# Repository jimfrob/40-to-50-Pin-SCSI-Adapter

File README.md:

I had a spare PowerBook version of a BlueSCSI v2 and wanted to make use of it, so I designed a PCB to adapt the 40-pin connector of the PowerBook to the standard 50-pin connector. I then designed a mount for installing it in a computer. The BlueSCSI is intended to be soldered on top of the board with the 40-pin header between. The power connector may be extranneous since the BlueSCSI should be able to take termination power.

40-pin header: Digikey part number [62004021121](https://www.digikey.com/en/products/detail/würth-elektronik/62004021121/15672211?s=N4IgTCBcDaIGxgAyICyLARg5kBdAvkA)

50-pin header: Digikey part number [SBH11-PBPC-D25-ST-BK](https://www.digikey.com/en/products/detail/sullins-connector-solutions/SBH11-PBPC-D25-ST-BK/1990069?s=N4IgTCBcDaIMoCEASBGFBaACgzBhdAImAKzpwAq6CA0iALoC%2BQA)

Any 4-pin header should work for power for use with a floppy drive berg connector.

The board was designed with KiCad 8.

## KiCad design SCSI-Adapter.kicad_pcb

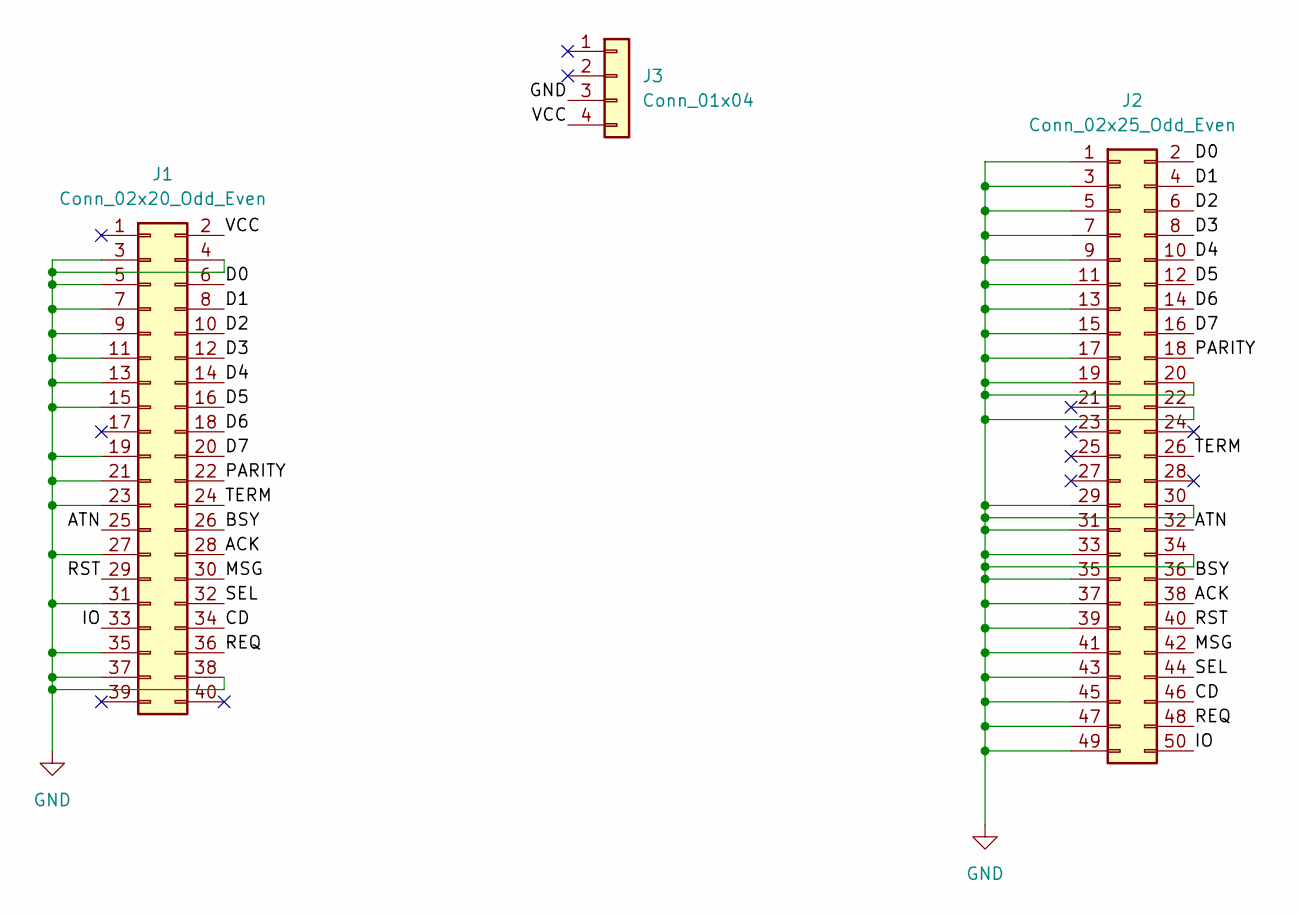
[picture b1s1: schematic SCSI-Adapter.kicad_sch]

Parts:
J1: Conn_02x20_Odd_Even; PinHeader_2x20_P2.00mm_Vertical
J2: Conn_02x25_Odd_Even; IDC-Header_2x25_P2.54mm_Vertical
J3: Conn_01x04; PinHeader_1x04_P2.54mm_Vertical

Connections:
/ACK: J1.28, J2.38
/ATN: J1.25, J2.32
/BSY: J1.26, J2.36
/CD: J1.34, J2.46
/D0: J1.6, J2.2
/D1: J1.8, J2.4
/D2: J1.10, J2.6
/D3: J1.12, J2.8
/D4: J1.14, J2.10
/D5: J1.16, J2.12
/D6: J1.18, J2.14
/D7: J1.20, J2.16
/IO: J1.33, J2.50
/MSG: J1.30, J2.42
/PARITY: J1.22, J2.18
/REQ: J1.36, J2.48
/RST: J1.29, J2.40
/SEL: J1.32, J2.44
/TERM: J1.24, J2.26
/VCC: J1.2, J3.4
GND: J1.3, J1.4, J1.5, J1.7, J1.9, J1.11, J1.13, J1.15, J1.19, J1.21, J1.23, J1.27, J1.31, J1.35, J1.37, J1.38, J2.1, J2.3, J2.5, J2.7, J2.9, J2.11, J2.13, J2.15, J2.17, J2.19, J2.20, J2.22, J2.29, J2.30, J2.31, J2.33, J2.34, J2.35, J2.37, J2.39, J2.41, J2.43, J2.45, J2.47, J2.49, J3.3

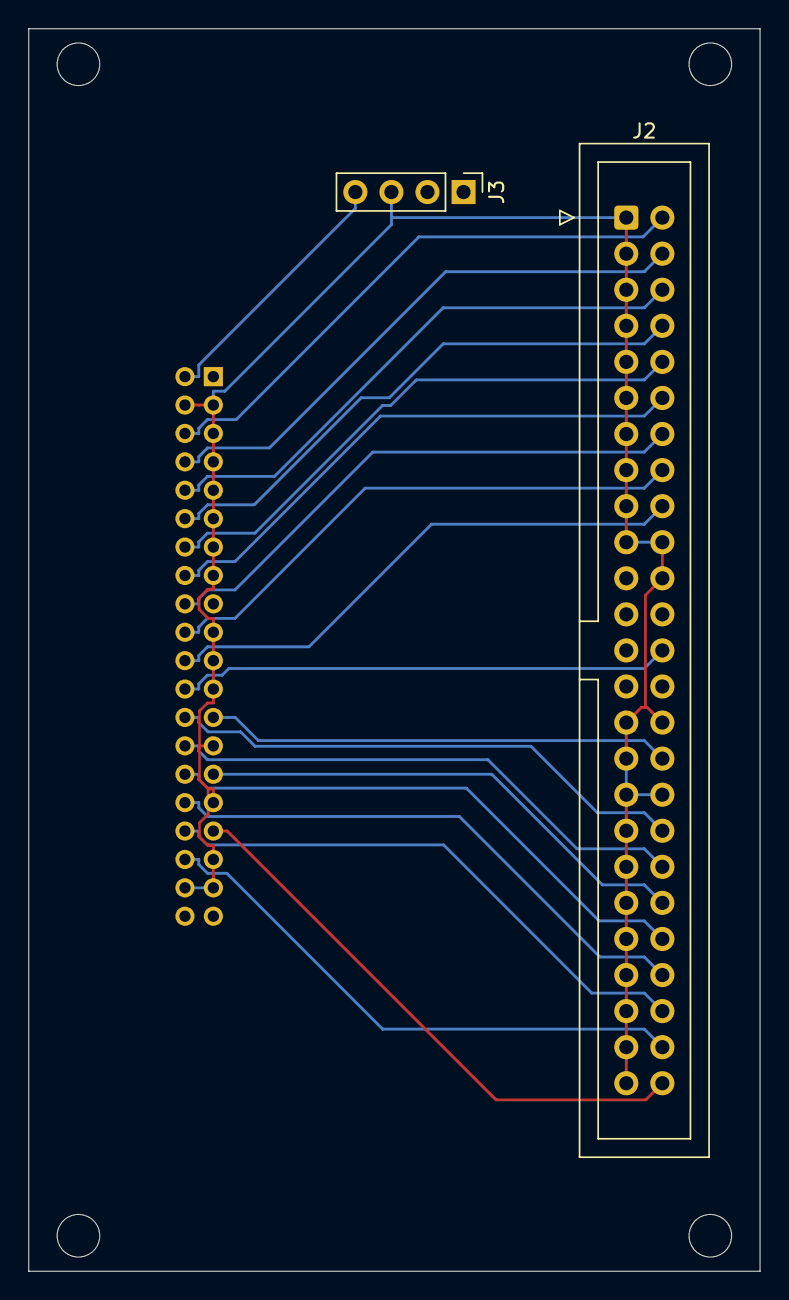
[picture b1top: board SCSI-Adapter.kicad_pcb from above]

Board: 2 copper layers, 51.5 x 87.5 mm, 3 parts (1 on the bottom side), 21 nets.

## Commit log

2024-04-03 Rename SCSI-Adapter.zip to Gerbers.zip
